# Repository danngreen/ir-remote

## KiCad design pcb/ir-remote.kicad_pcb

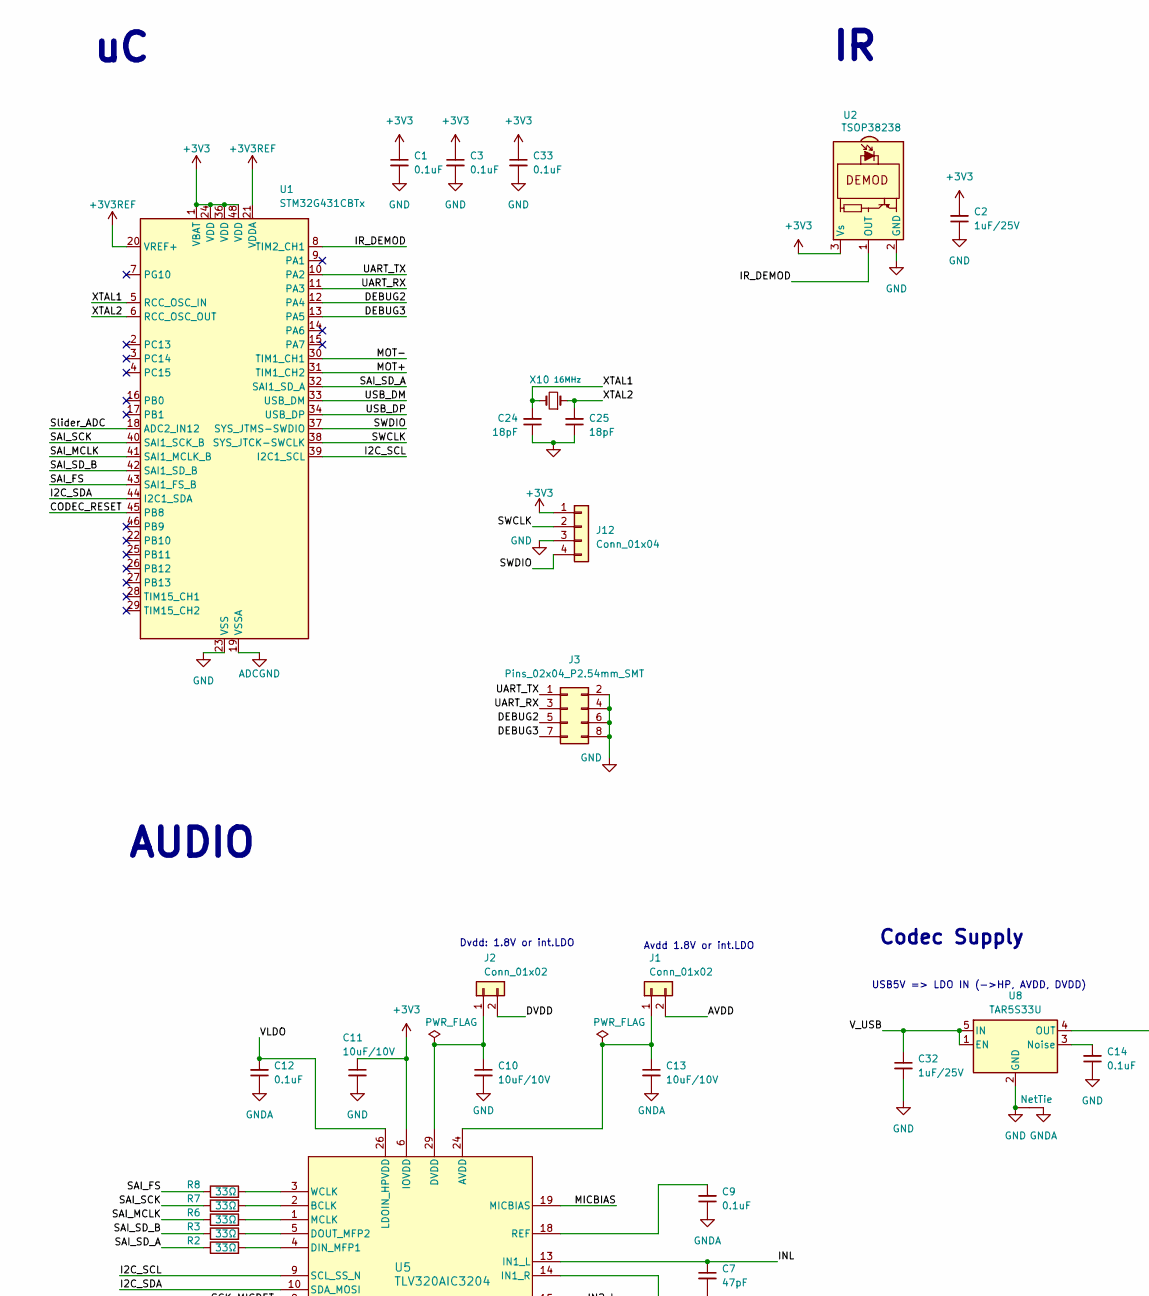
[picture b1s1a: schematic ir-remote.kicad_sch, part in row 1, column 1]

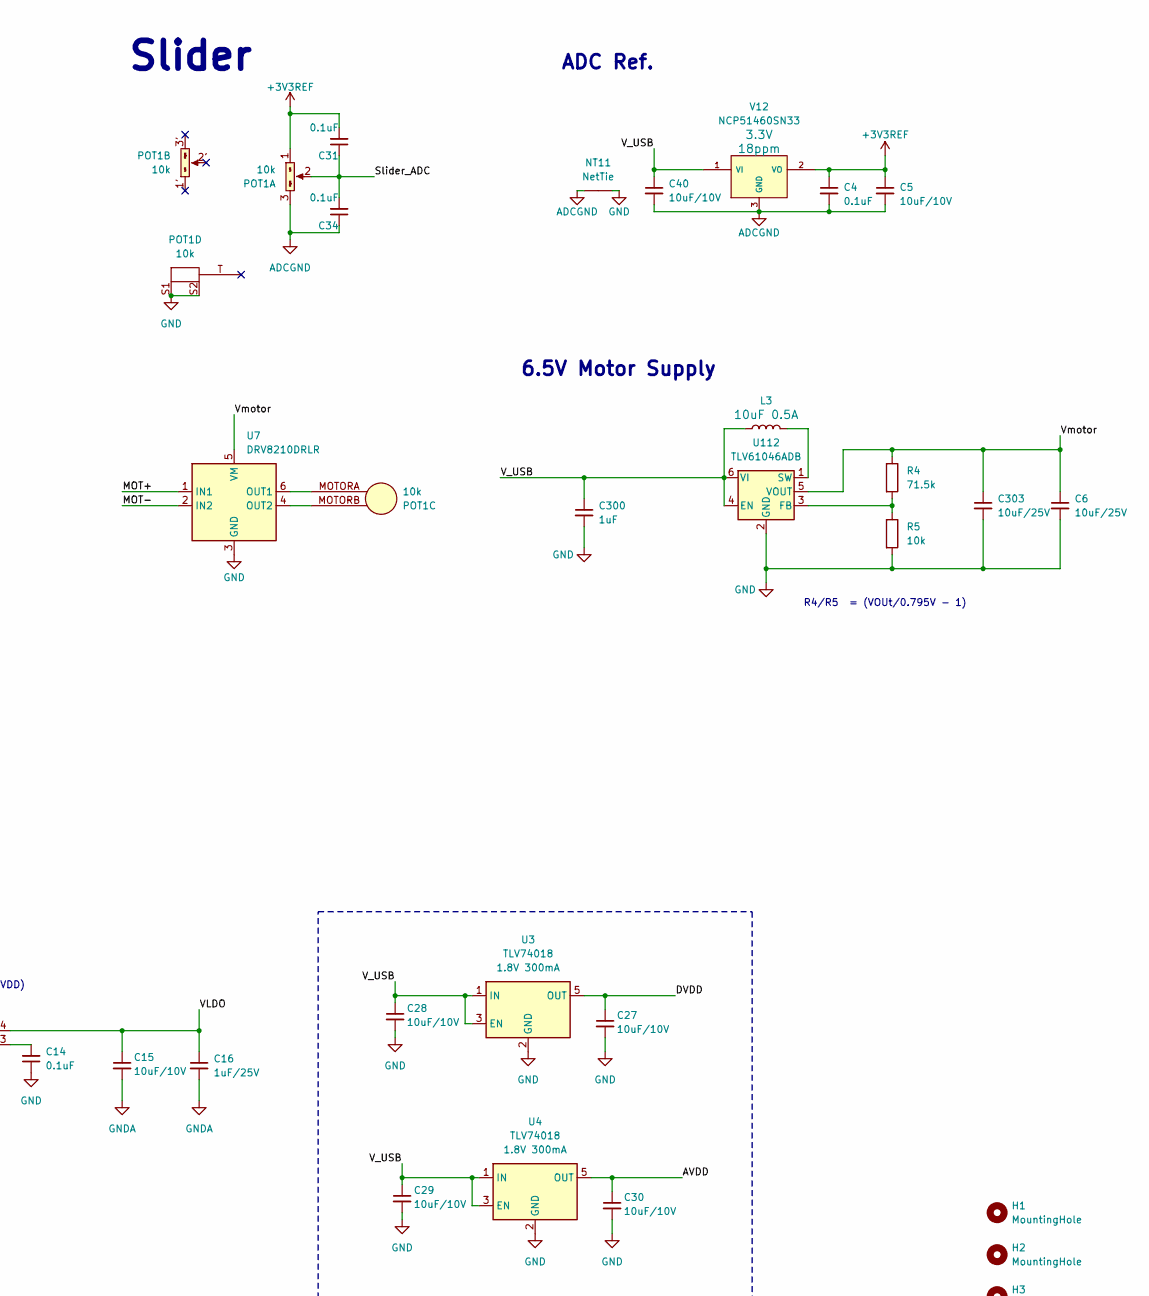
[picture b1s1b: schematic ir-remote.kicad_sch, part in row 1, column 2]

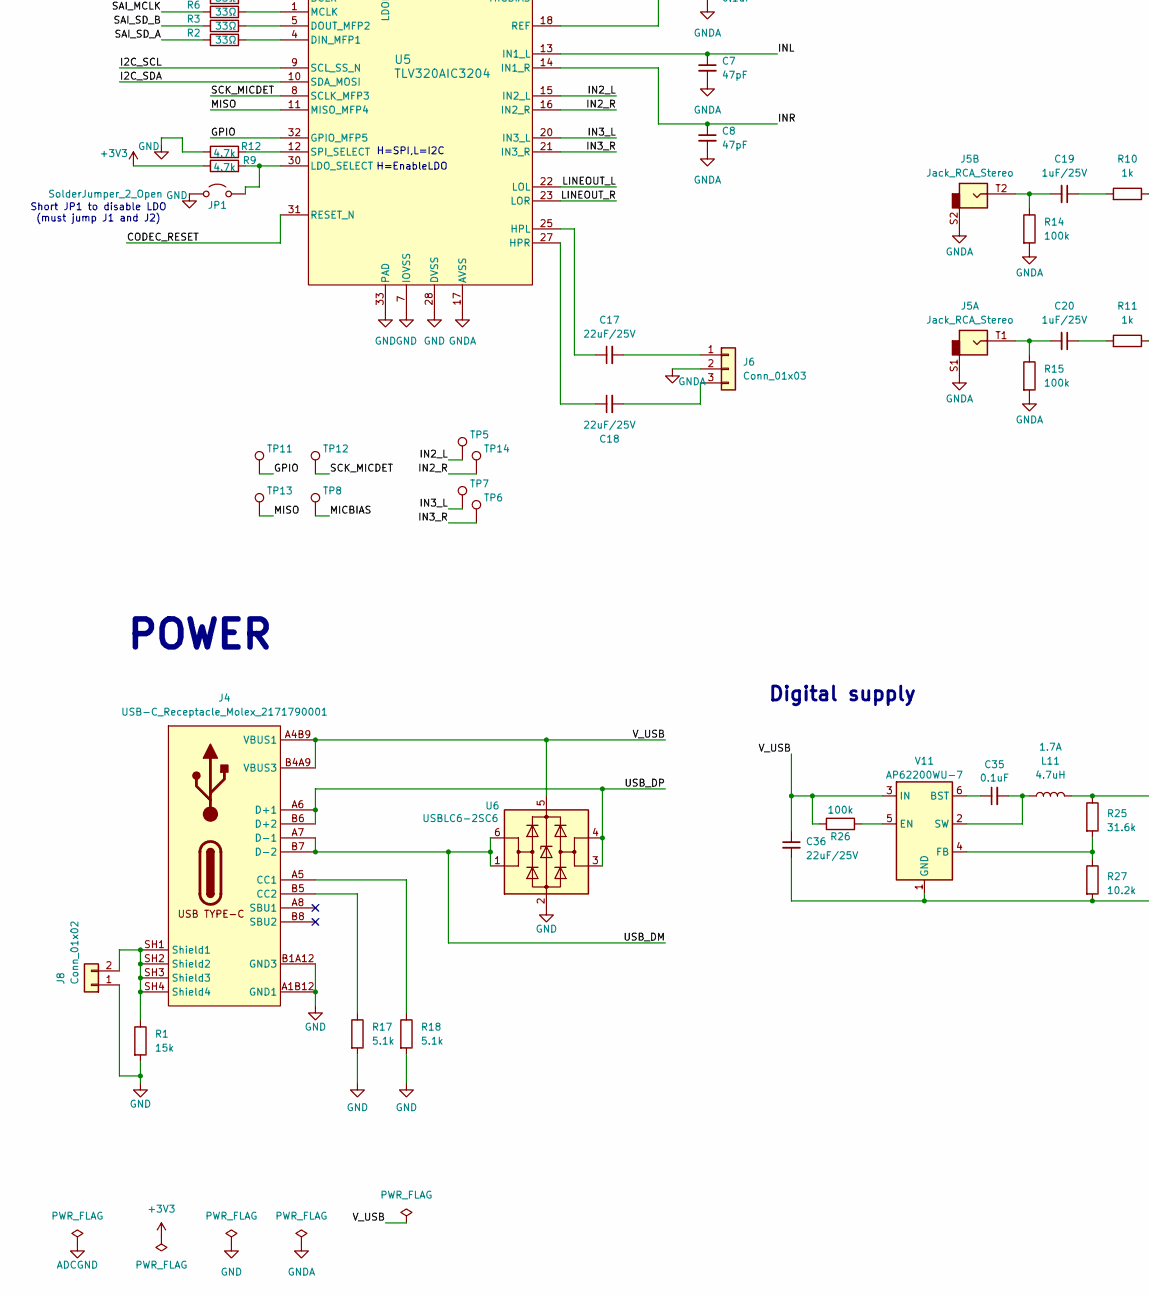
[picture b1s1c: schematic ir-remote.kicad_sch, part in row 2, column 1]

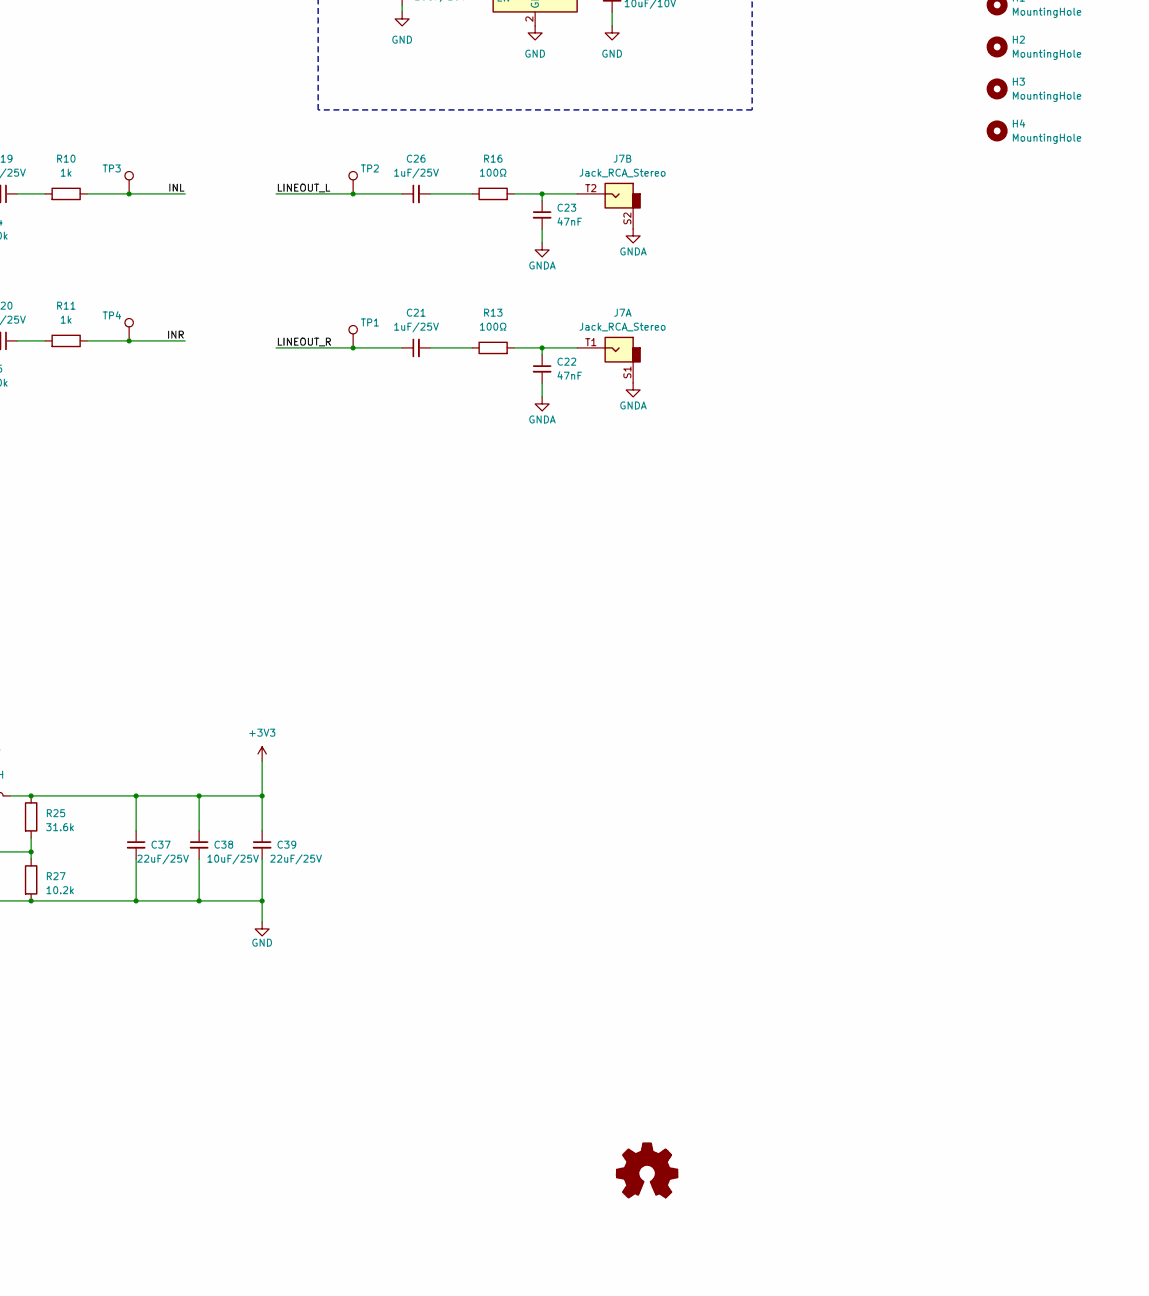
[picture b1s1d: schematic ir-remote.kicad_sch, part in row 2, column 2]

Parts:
C1, C3, C9, C12, C14, C33: 0.1uF_0603_16V; C_0603; Part Number 0603YC104KAT2A; JLCPCB ID C14663
C2, C16, C19, C20, C21, C26, C32: 1uF_0603_25V; C_0603; Part Number GRM188R61E105KA12D; JLCPCB ID C15849
C4, C31, C34, C35: 100nF_0603_16V; C_0603; Part Number 0603YC104KAT2A; JLCPCB ID C14663
C5, C10, C11, C13, C15, C27, C28, C29, C30, C40: 10uF_0603_10V; C_0603; Part Number GRM188R61A106KE69D; JLCPCB ID C19702
C6, C38, C303: 10uF_0805_25V; C_0805; Part Number GRM21BR61E106MA73L; JLCPCB ID C15850
C7, C8: 47pF_0603_50V; C_0603; Part Number CC0603JRNPO9BN470; JLCPCB ID C1671
C17, C18, C36, C37, C39: 22uF_1206_25V; C_1206; Part Number TMK316BBJ226ML-T; JLCPCB ID C12891
C22, C23: 47nF_0603_35V; C_0603; Part Number CC0603KRX7R9BB473; JLCPCB ID C1622
C24, C25: 18pF_0603_50V; C_0603; Part Number C0603C180J5GACTU; JLCPCB ID C1647
C300: 1uF_0402_25V; C_0402; Part Number GMK105CC6105KV-F; JLCPCB ID C52923
H1, H2, H3, H4: MountingHole; MountingHole_Screw_3mmHole_5.3mmHead
J1, J2, J8: Conn_01x02; Pins_1x02_2.54mm_TH; Part Number 1-0201FBV0T
J3: Pins_02x04_P2.54mm_SMT; Pins_2x04_P2.54mm_Vertical_SMD; Part Number TSM-104-01-F-DV
J4: USB-C_Receptacle_Molex_2171790001; USB_C_Receptacle_Molex_2171790001; Part Number 217179-0001; JLCPCB ID C2894899
J5, J7: Jack_RCA_Stereo; RCA_Stereo_SwitchCraft-PJRAS2X1S; Part Number PJRAS2X1S01AUX
J6: Conn_01x03; Pins_1x03_2.54mm_TH; Part Number 1-0301FBV0T
J12: Conn_01x04; Pins_1x04_2.54mm_TH_SWD; Part Number 1-0401FBV0T
JP1: SolderJumper_2_Open; JUMPER_SMD_1x2
L3: 10uH_0805_0.5A; R_0805_2012Metric; Part Number MLZ2012N100L; JLCPCB ID C88182
L11: 4.7uH_1.2A_40xx; L_Taiyo-Yuden_NR-40xx; Part Number NRS4018T4R7MDGJ; JLCPCB ID C92936
NT2, NT11: NetTie; NetTie-2_SMD_Pad0.16mm_6mil; Part Number Do Not Place
POT1: Slider_Dual_Motorized_PSM60-081A-xxx; Part Number PSM60-081A-103B2
R1: 15k_0603; R_0603; Part Number RC0603FR-0715KL; JLCPCB ID C114661
R2, R3, R6, R7, R8: 33Ω_0603; R_0603; Part Number RC0603FR-0733RL; JLCPCB ID C23140
R4: 71.5k_0603; R_0603; Part Number RC0603FR-0771K5L; JLCPCB ID C185312
R5: 10k_0603; R_0603; Part Number RC0603FR-0710KL; JLCPCB ID C98220
R9, R12: 4.7k_0603; R_0603; Part Number RC0603FR-074K7L; JLCPCB ID C99782
R10, R11: 1k_0603; R_0603; Part Number RC0603FR-071KL; JLCPCB ID C22548
R13, R16: 100Ω_0603; R_0603; Part Number RC0603FR-07100RL; JLCPCB ID C105588
R14, R15, R26: 100k_0603; R_0603; Part Number RC0603FR-07100KL; JLCPCB ID C14675
R17, R18: 5.1k_0603; R_0603; Part Number RC0603FR-075K1L; JLCPCB ID C105580
R25: 31.6k_0603; R_0603; Part Number RC0603FR-0731K6L; JLCPCB ID C185339
R27: 10.2k_0603; R_0603; Part Number RC0603FR-0710K2L; JLCPCB ID C183219
TP1, TP2, TP3, TP4, TP5, TP6, TP7, TP8, TP11, TP12, TP13, TP14: TestPoint; TestPoint_WireHole
U1: STM32G431CBTx; LQFP-48_7x7mm_P0.5mm; JLCPCB ID C529355
U2: TSOP38238; Vishay_MINICAST-3Pin
U3, U4: TLV74018; SOT-23-5; Part Number TLV74018PDBVR; JLCPCB ID C3746861
U5: TLV320AIC3204; QFN-32-1EP_5x5mm_P0.5mm_EP3.45x3.45mm_ThermalVias; Part Number TLV320AIC3204IRHBR; JLCPCB ID C24109
U6: USBLC6-2SC6; SOT-23-6; Part Number USBLC6-2SC6; JLCPCB ID C2827654
U7: DRV8210DRLR; SOT-563; Part Number DRV8210DRLR; JLCPCB ID C3681297
U8: TAR5S33U; SOT-563-5; Part Number TAR5S33UTE85LF; JLCPCB ID C3745113
U112: TLV61046ADB; SOT-23-6; Part Number TLV61046ADBVR; JLCPCB ID C464815
V11: AP62200WU-7; TSOT-23-6; Part Number AP62200WU7; JLCPCB ID C1323282
V12: NCP51460SN33; SOT23-3_PO132; Part Number NCP51460SN33T1G; JLCPCB ID C233715
X10: 16MHz_18pF_FA238; FA-238; Part Number TSX-3225 16.0000MF18X-AC3; JLCPCB ID C90906

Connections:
+3V3: C1.1, C2.2, C3.1, C11.1, C33.1, C37.1, C38.1, C39.1, J12.1, L11.2, R9.1, R25.1, U1.1 (VBAT), U1.24 (VDD), U1.36 (VDD), U1.48 (VDD), U2.3 (Vs), U5.6 (IOVDD)
+3V3REF: C4.1, C5.1, C31.2, POT1.1 (Left), U1.20 (VREF+), U1.21 (VDDA), V12.2 (VO)
/AVDD: C30.1, J1.2, U4.5 (OUT)
/CODEC_RESET: U1.45 (PB8), U5.31 (RESET_N)
/DEBUG2: J3.5, U1.12 (PA4)
/DEBUG3: J3.7, U1.13 (PA5)
/DVDD: C27.1, J2.2, U3.5 (OUT)
/GPIO: TP11.1, U5.32 (GPIO_MFP5)
/I2C_SCL: U1.39 (I2C1_SCL), U5.9 (SCL_SS_N)
/I2C_SDA: U1.44 (I2C1_SDA), U5.10 (SDA_MOSI)
/IN2_L: TP5.1, U5.15 (IN2_L)
/IN2_R: TP14.1, U5.16 (IN2_R)
/IN3_L: TP7.1, U5.20 (IN3_L)
/IN3_R: TP6.1, U5.21 (IN3_R)
/INL: C7.1, R10.1, TP3.1, U5.13 (IN1_L)
/INR: C8.1, R11.1, TP4.1, U5.14 (IN1_R)
/IR_DEMOD: U1.8 (TIM2_CH1), U2.1 (OUT)
/LINEOUT_L: C26.1, TP2.1, U5.22 (LOL)
/LINEOUT_R: C21.1, TP1.1, U5.23 (LOR)
/MICBIAS: TP8.1, U5.19 (MICBIAS)
/MISO: TP13.1, U5.11 (MISO_MFP4)
/MOT+: U1.31 (TIM1_CH2), U7.1 (IN1)
/MOT-: U1.30 (TIM1_CH1), U7.2 (IN2)
/SAI_FS: R8.1, U1.43 (SAI1_FS_B)
/SAI_MCLK: R6.1, U1.41 (SAI1_MCLK_B)
/SAI_SCK: R7.1, U1.40 (SAI1_SCK_B)
/SAI_SD_A: R2.1, U1.32 (SAI1_SD_A)
/SAI_SD_B: R3.1, U1.42 (SAI1_SD_B)
/SCK_MICDET: TP12.1, U5.8 (SCLK_MFP3)
/SWCLK: J12.2, U1.38 (SYS_JTCK-SWCLK)
/SWDIO: J12.4, U1.37 (SYS_JTMS-SWDIO)
/Slider_ADC: C31.1, C34.2, POT1.2 (Center), U1.18 (ADC2_IN12)
/UART_RX: J3.3, U1.11 (PA3)
/UART_TX: J3.1, U1.10 (PA2)
/USB_DM: J4.A7 (D-1), J4.B7 (D-2), U1.33 (USB_DM), U6.1 (I/O1), U6.6 (I/O1)
/USB_DP: J4.A6 (D+1), J4.B6 (D+2), U1.34 (USB_DP), U6.3 (I/O2), U6.4 (I/O2)
/VLDO: C12.2, C15.1, C16.1, U5.26 (LDOIN_HPVDD), U8.4 (OUT)
/V_USB: C28.1, C29.1, C32.1, C36.1, C40.1, C300.1, J4.A4B9 (VBUS1), J4.B4A9 (VBUS3), L3.1, R26.1, U3.1 (IN), U3.3 (EN), U4.1 (IN), U4.3 (EN), U6.5 (VBUS), U8.1 (EN), U8.5 (IN), U112.4 (EN), U112.6 (VI), V11.3 (IN), V12.1 (VI)
/Vmotor: C6.1, C303.1, R4.1, U7.5 (VM), U112.5 (VOUT)
/XTAL1: C24.2, U1.5 (RCC_OSC_IN), X10.2
/XTAL2: C25.2, U1.6 (RCC_OSC_OUT), X10.1
ADCGND: C4.2, C5.2, C34.1, C40.2, NT11.1, POT1.3 (Right), U1.19 (VSSA), V12.3 (GND)
GND: C1.2, C2.1, C3.2, C6.2, C10.2, C11.2, C14.1, C24.1, C25.1, C27.2, C28.2, C29.2, C30.2, C32.2, C33.2, C36.2, C37.2, C38.2, C39.2, C300.2, C303.2, J3.2, J3.4, J3.6, J3.8, J4.A1B12 (GND1), J4.B1A12 (GND3), J8.1, J12.3, JP1.1 (A), NT2.1, NT11.2, POT1.S1 (GND), POT1.S2 (GND), R1.2, R5.2, R12.1, R17.2, R18.2, R27.2, U1.23 (VSS), U1.35 (VSS), U1.47 (VSS), U2.2 (GND), U3.2 (GND), U4.2 (GND), U5.7 (IOVSS), U5.28 (DVSS), U5.33 (PAD), U6.2 (GND), U7.3 (GND), U8.2 (GND), U112.2 (GND), V11.1 (GND)
GNDA: C7.2, C8.2, C9.1, C12.1, C13.2, C15.2, C16.2, C22.2, C23.2, J5.S1, J5.S2, J6.2, J7.S1, J7.S2, NT2.2, R14.2, R15.2, U5.17 (AVSS)
unnamed: C19.1, R10.2
unnamed: C19.2, J5.T2, R14.1
unnamed: C20.1, R11.2
unnamed: C20.2, J5.T1, R15.1
unnamed: C21.2, R13.1
unnamed: C22.1, J7.T1, R13.2
unnamed: C23.1, J7.T2, R16.2
unnamed: C26.2, R16.1
unnamed: C13.1, J1.1, U5.24 (AVDD)
unnamed: C10.1, J2.1, U5.29 (DVDD)
unnamed: J4.A5 (CC1), R18.1
unnamed: J4.B5 (CC2), R17.1
unnamed: J4.SH1 (Shield1), J4.SH2 (Shield2), J4.SH3 (Shield3), J4.SH4 (Shield4), J8.2, R1.1
unnamed: C17.2, J6.1
unnamed: C18.2, J6.3
unnamed: JP1.2 (B), R9.2, U5.30 (LDO_SELECT)
unnamed: R7.2, U5.2 (BCLK)
unnamed: R2.2, U5.4 (DIN_MFP1)
unnamed: R3.2, U5.5 (DOUT_MFP2)
unnamed: C17.1, U5.25 (HPL)
unnamed: C18.1, U5.27 (HPR)
unnamed: R6.2, U5.1 (MCLK)
unnamed: C9.2, U5.18 (REF)
unnamed: R12.2, U5.12 (SPI_SELECT)
unnamed: R8.2, U5.3 (WCLK)
unnamed: POT1.MOTORA, U7.6 (OUT1)
unnamed: POT1.MOTORB, U7.4 (OUT2)
unnamed: C14.2, U8.3 (Noise)
unnamed: R4.2, R5.1, U112.3 (FB)
unnamed: L3.2, U112.1 (SW)
unnamed: C35.1, V11.6 (BST)
unnamed: R26.2, V11.5 (EN)
unnamed: R25.2, R27.1, V11.4 (FB)
unnamed: C35.2, L11.1, V11.2 (SW)

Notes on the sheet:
H=SPI,L=I2C
Slider
Codec Supply
R4/R5 = (VOUt/0.795V - 1)
POWER
H=EnableLDO
Digital supply
Dvdd: 1.8V or int.LDO
USB5V => LDO IN (->HP, AVDD, DVDD)
Avdd 1.8V or int.LDO
Short JP1 to disable LDO (must jump J1 and J2)
AUDIO
6.5V Motor Supply
ADC Ref.

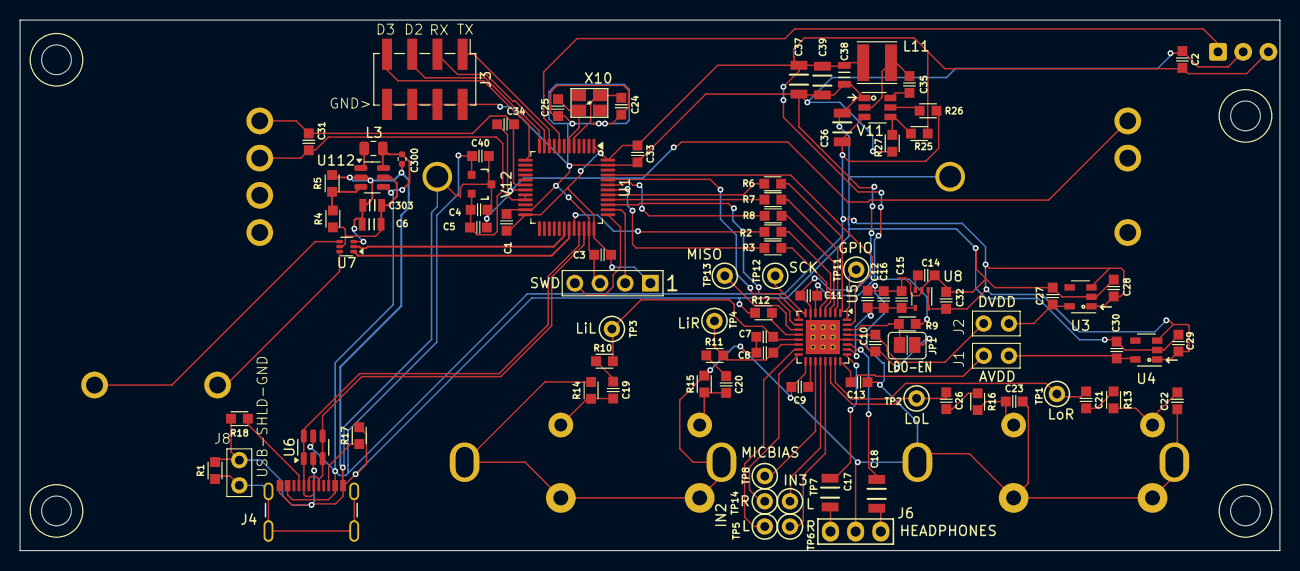
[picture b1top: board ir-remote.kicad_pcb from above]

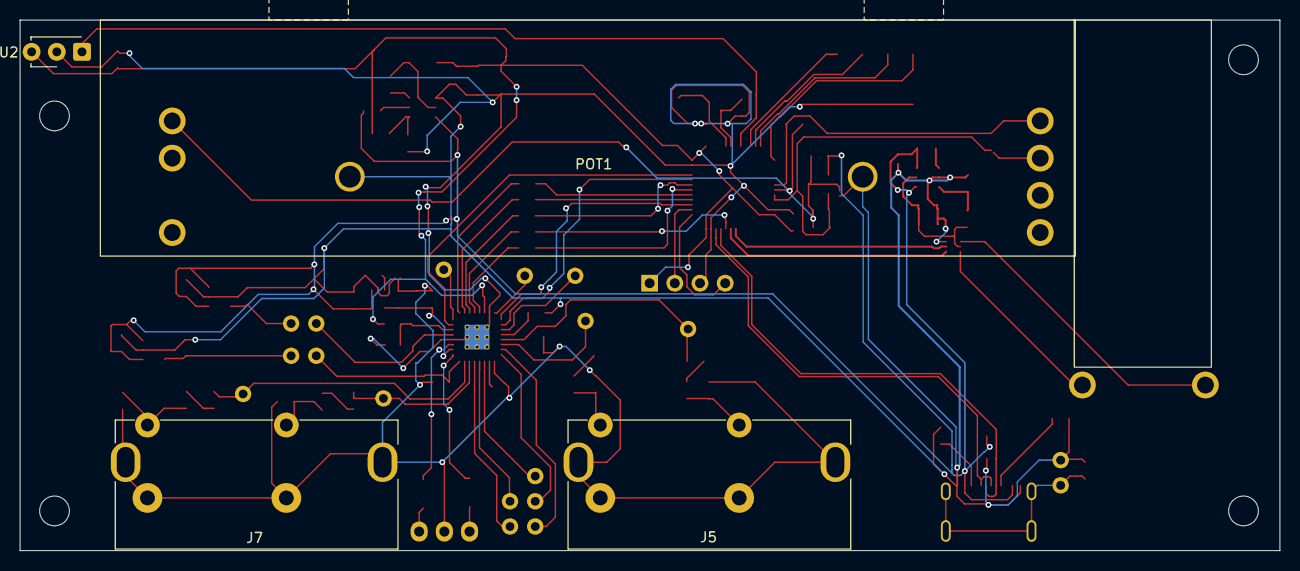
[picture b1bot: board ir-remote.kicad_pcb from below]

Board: 2 copper layers, 127.0 x 53.5 mm, 106 parts (4 on the bottom side), 78 nets.

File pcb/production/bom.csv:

Designator,Footprint,Quantity,Value,LCSC Part #
"C1, C12, C14, C3, C33, C9",C_0603,6,0.1uF_0603_16V,C14663
"C10, C11, C13, C15, C27, C28, C29, C30, C40, C5",C_0603,10,10uF_0603_10V,C19702
"C16, C19, C2, C20, C21, C26, C32",C_0603,7,1uF_0603_25V,C15849
"C17, C18, C36, C37, C39",C_1206,5,22uF_1206_25V,C12891
"C22, C23",C_0603,2,47nF_0603_35V,C1622
"C24, C25",C_0603,2,18pF_0603_50V,C1647
C300,C_0402,1,1uF_0402_25V,C52923
"C303, C38, C6",C_0805,3,10uF_0805_25V,C15850
"C31, C34, C35, C4",C_0603,4,100nF_0603_16V,C14663
"C7, C8",C_0603,2,47pF_0603_50V,C1671
"J1, J2, J8",Pins_1x02_2.54mm_TH,3,Conn_01x02,
J12,Pins_1x04_2.54mm_TH_SWD,1,Conn_01x04,
J3,Pins_2x04_P2.54mm_Vertical_SMD,1,Pins_02x04_P2.54mm_SMT,
J4,USB_C_Receptacle_Molex_2171790001,1,USB-C_Receptacle_Molex_2171790001,C2894899
"J5, J7",RCA_Stereo_SwitchCraft-PJRAS2X1S,2,Jack_RCA_Stereo,
J6,Pins_1x03_2.54mm_TH,1,Conn_01x03,
L11,L_Taiyo-Yuden_NR-40xx,1,4.7uH_1.2A_40xx,C92936
L3,0805,1,10uH_0805_0.5A,C88182
POT1,Slider_Dual_Motorized_PSM60-081A-xxx,1,Slider_Dual_Motorized_PSM60-081A-xxx,
R1,R_0603,1,15k_0603,C114661
"R10, R11",R_0603,2,1k_0603,C22548
"R12, R9",R_0603,2,4.7k_0603,C99782
"R13, R16",R_0603,2,100Ω_0603,C105588
"R14, R15, R26",R_0603,3,100k_0603,C14675
"R17, R18",R_0603,2,5.1k_0603,C105580
"R2, R3, R6, R7, R8",R_0603,5,33Ω_0603,C23140
R25,R_0603,1,31.6k_0603,C185339
R27,R_0603,1,10.2k_0603,C183219
R4,R_0603,1,71.5k_0603,C185312
R5,R_0603,1,10k_0603,C98220
"TP1, TP11, TP12, TP13, TP14, TP2, TP3, TP4, TP5, TP6, TP7, TP8",TestPoint_WireHole,12,TestPoint,
U1,LQFP-48_7x7mm_P0.5mm,1,STM32G431CBTx,C529355
U112,SOT-23-6,1,TLV61046ADB,C464815
U2,Vishay_MINICAST-3Pin,1,TSOP38238,
"U3, U4",SOT-23-5,2,TLV74018,C3746861
U5,QFN-32-1EP_5x5mm_P0.5mm_EP3.45x3.45mm_ThermalVias,1,TLV320AIC3204,C24109
U6,SOT-23-6,1,USBLC6-2SC6,C2827654
U7,SOT-563,1,DRV8210DRLR,C3681297
U8,SOT-563-5,1,TAR5S33U,C3745113
V11,TSOT-23-6,1,AP62200WU-7,C1323282
V12,SOT23-3_PO132,1,NCP51460SN33,C233715 
X10,FA-238,1,16MHz_18pF_FA238,C90906

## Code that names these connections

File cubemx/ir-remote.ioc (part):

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Mcu.Name=STM32G431C(6-8-B)Tx
Mcu.Package=LQFP48
Mcu.UserName=STM32G431CBTx
PA10.Mode=SAI_A_SyncSlave
PA10.Signal=SAI1_SD_A
PA11.Mode=Device
PA11.Signal=USB_DM
PA12.Mode=Device
PA12.Signal=USB_DP
PA13.Mode=Serial_Wire
PA13.Signal=SYS_JTMS-SWDIO
PA14.Mode=Serial_Wire
PA14.Signal=SYS_JTCK-SWCLK
PA15.Mode=I2C
PA15.Signal=I2C1_SCL
PA2.Mode=Asynchronous
PA2.Signal=USART2_TX
PA3.Mode=Asynchronous
PA3.Signal=USART2_RX
PB2.Mode=IN12-Single-Ended
PB2.Signal=ADC2_IN12
PB3.Mode=SAI_B_MasterWithClock
PB3.Signal=SAI1_SCK_B
PB4.Mode=SAI_B_MasterWithClock
PB4.Signal=SAI1_MCLK_B
PB5.Mode=SAI_B_MasterWithClock
PB5.Signal=SAI1_SD_B
PB6.Mode=SAI_B_MasterWithClock
PB6.Signal=SAI1_FS_B
PB7.Mode=I2C
PB7.Signal=I2C1_SDA
PF0-OSC_IN.Mode=HSE-External-Oscillator
PF0-OSC_IN.Signal=RCC_OSC_IN
PF1-OSC_OUT.Mode=HSE-External-Oscillator
PF1-OSC_OUT.Signal=RCC_OSC_OUT
RCC.HSE_VALUE=16000000
RCC.SYSCLKFreq_VALUE=170000000
RCC.SYSCLKSource=RCC_SYSCLKSOURCE_PLLCLK
board=custom

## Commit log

2025-12-07 Add cubemx-generated project
2025-12-07 Add minipeg low-level stuff (not in use)
2025-12-07 Add nec decoding logic
2025-12-07 Format main
2025-12-07 Format _it
2025-12-07 Move nec.h/c
2025-12-07 Add capture.c
2025-12-07 Adjust htim periph setup
2025-12-07 Enable TIM2 IRQ to use HAL
2025-12-07 Format CmakeLists and add new sources
2025-12-07 Ignore build
2025-12-07 Convert business-logic code to c++
2025-12-07 Format _msp
2025-12-08 Add cpputil submodule
2025-12-08 Made ir receiver into a class
    Revert edits to stm32cubemx/CMakeLists (except main.c=>main.cc)
2025-12-08 Move hal init to own file
2025-12-08 Add mdrivlib submodule
2025-12-12 Proof of concept to receive vol up/down signals
2025-12-15 Add schematic and PCB (WIP)
2025-12-19 PCB WIP
2026-01-02 PCB routed and ready for review
2026-01-02 cubemx updated
2026-01-02 Adjust PCB edges and mounting holes to fit enclosure
2026-01-02 Enclosure 3D started
2026-01-02 Exported JLCPCB production files
2026-01-02 WIP Enclosure
2026-01-02 Remove rounded corners on PCB
2026-01-03 Enclosure and PCB matched and fit
2026-01-03 PCB: add missing 5.1k USB pull-downs
2026-01-04 Enclosure ordered
2026-01-04 pcb: 20R=>33R, 2.2uF=>10uF. Change some JLC # to cheaper parts
2026-01-04 Added JLC pcb files downloaded after ordering
    Since several parts substitutions were made, this will help clarify
2026-01-19 Re-arrange files so we can add mdrivlib
2026-01-19 WIP: Adding mdrivlib
2026-01-19 Update mdrivlib (add stm32g4 arch)
2026-01-19 Migrate libs from ir-remote/ to firmware/
2026-01-19 Note on PCB about jumper
2026-01-19 Migrating to firmware/
2026-01-19 CI script
2026-01-19 Update mdrivlib (g4 branch)
2026-01-19 Update cpputil (latest)
2026-01-20 Building with new structure
2026-01-20 Update mdrivlib (more g4 support)
2026-01-20 Re-export auto-generated project
2026-01-20 Update mdrivlib (g4 isrs)
2026-01-20 Cleanup
2026-01-20 Build isrs
2026-01-20 Motor test
2026-01-20 trace32 script
2026-01-20 ADC reading with DMA
2026-01-20 Update mdrivlib (ADC reading)
2026-01-20 I2C(working) and SAI(WIP)
2026-01-20 Update mdrivlib (SAI and I2C)
2026-01-20 jdebug project file
2026-02-10 Update mdrivlib (sai cleanup)
2026-02-10 Remove unused
2026-02-10 Main: adc sets volume, used in audio callback
2026-02-10 RCC: 170MHz
2026-02-11 Update mdrivlib (g4)
2026-02-11 Update cpputil (latest main)
2026-02-11 Re-arrange files
2026-02-11 Controls returns adc values in separate TU
    Gets around the compilers aggressive optimization of adc value without need to use volatile
2026-02-11 Add printf() support
2026-02-11 Remove unused HAL .c files
2026-02-11 Don't over-align audio buffers
2026-02-11 Adjust optimization settings
    -Ofast might make math errors, so we stick with O2
2026-02-11 Log startup to console
2026-02-11 Make test audio class (not in use, but available to test on home system)
2026-02-11 SCH: saved in latest kicad (no changes)
2026-02-11 Change project namespace => RemoteVolume
2026-02-11 Start IR Capture class
2026-05-29 Update mdrivlib (add UART sync flag)
2026-05-29 Add console RX to send up/down events
2026-05-29 Init motor pins low
2026-05-29 Update mdrivlib (ADC1/2 aliases)
2026-05-29 Controls polls events and moves motor up/down
2026-05-29 Add IR decoding (WIP)
2026-05-29 Implement IR capturing of vol up/down
2026-05-29 Implement Mute on the remote
2026-05-29 Implement "repeat" remote button being held down
2026-05-29 Rename ir-remote to cubemx
2026-05-29 Fix dropped repeats
2026-05-29 Hold/repeat goes into PWM mode to continously drive the motor
2026-05-29 Set ADC min/max away from rails and scale volume accordingly
2026-05-29 Remove hold-to-repeat (remote does it)
